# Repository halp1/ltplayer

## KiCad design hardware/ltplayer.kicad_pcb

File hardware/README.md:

# ltplayer hardware

KiCad 10 project, second board layout. Schematic and 4-layer layout are done
and pass ERC and DRC with schematic parity. Not yet fabricated.

| Sheet | Contents |
| --- | --- |
| Power | USB4105 USB-C (5.1k CC pull-downs, USBLC6 ESD), BQ24074 1S LiPo charger with power path (1 A charge, 1.5 A input), soft power latch, TLV75533 3.3 V, TLV62569 buck to 2.0 V feeding two TPS7A2018 1.8 V LDOs (digital `+1V8`, analog `+1V8A`), battery solder pads plus an optional side-entry SMD JST-PH |
| MCU | STM32U575ZIT6Q (SMPS variant, 2.2 uH on VLXSMPS), 16 MHz crystal for USB DFU, decoupling, BOOT0 pull-down, NRST cap, battery and VBUS sense dividers, ten buttons |
| Peripherals | Hirose DM3AT microSD on SDMMC1 4-bit with 47k pull-ups, Newhaven NHD-2.4-240320AF-CSXP 2.4in IPS panel on a 40-pin FH12 on the back, 2N7002 backlight switch |
| Wireless | ESP32-MINI-1U (Bluetooth Classic A2DP, BLE, 2.4 GHz WiFi) on the back, own TLV75733 3.3 V regulator switched by the MCU, U.FL to a stick-on antenna |
| Audio | Two CS43131 (I2C 0x30 and 0x31), shared 22.5792 MHz 1.8 V oscillator for MCLK, PCA9306 I2C shifter, TXS0102 shifters on I2S, four TMUX4819 output switches, SJ1-3524N 3.5 mm and PJ-4450 4.4 mm jacks on the back |

## Pin map

Kept as close to the current firmware (`src/main.rs`) as possible.

| Function | Pin | Notes |
| --- | --- | --- |
| SDMMC1 D0 D1 D2 D3 CLK CMD | PC8 PC9 PC10 PC11 PC12 PD2 | unchanged |
| SD card detect | PF15 | low = card present |
| SPI1 SCK MOSI | PA5 PA7 | unchanged, panel MISO (SDO) not connected |
| TFT CS DC RST | PD14 PD15 PF12 | unchanged, 4-wire SPI strapped by IM0/IM1/IM2 |
| Backlight | PE11 | TIM1_CH2 PWM into Q301, high = on |
| Buttons up down left right | PE13 PE14 PA3 PA2 | front d-pad, active low with internal pull-up |
| Buttons play/pause back | PE10 PB0 | play/pause moved from PC3 so every button has its own EXTI line |
| Button menu | PE15 | active high, shares the BOOT0 net (see Flashing) |
| Buttons vol+ vol- | PE7 PE8 | right edge SKSC, active low with internal pull-up |
| Power button | PE12 | active high, VSYS through a 100k/200k divider |
| Power hold | PC13 | drive high at boot to keep the regulators on |
| SAI1 FS_A SCK_A SD_A | PE4 PE5 PE6 | |
| DAC INT | PE1 | moved from PE2, which shared an EXTI line with the right button |
| DAC reset control | PE3 | inverted through Q401: low releases reset, high or floating holds it |
| I2C1 SCL SDA | PB8 PB9 | |
| JACK_SEL | PG0 | low = 3.5 mm |
| Output switch enable | PG3 | SW_EN, high turns on all four TMUX4819, low mutes both jacks |
| Jack detect 3.5 mm, 4.4 mm | PG1, PG2 | |
| USB DM DP, VBUS sense | PA11 PA12, PA9 | |
| Battery sense | PA0 | VBAT / 2 |
| BOOT0 | PH3 | 10k to GND, the menu button pulls it to +3V3 |
| ESP32 UART (USART3 TX, RX) | PD8 PD9 | commands and ESP32 firmware updates |
| ESP32 I2S (SAI2_A SCK, SD, FS) | PD10 PD11 PD12 | MCU sends decoded audio to the ESP32 |
| ESP32 EN, BOOT, radio power | PD13 PG13 PG14 | PG14 high turns on the ESP32's 3.3 V regulator |
| HSE | PH0 PH1 | 16 MHz crystal Y201 |

## Power

The slide switch is gone. SW101 pulls `PWR_EN` up from VSYS through D103, which
starts all three regulators. Firmware then drives PC13 high, which holds
`PWR_EN` through D104, so the board stays on after the button is released. To
power off, drive PC13 low. R107 pulls `PWR_EN` down so the board stays off
while the button is up. PE12 reads the button through a divider so it also
works as a normal input while running.

USB power also holds `PWR_EN` through R110 and D105, so a plugged-in board
stays on whatever the firmware does. If the user switches off while it is
plugged in, firmware should turn the screen off and sleep.

The BQ24074 runs the system from USB and charges the battery at the same
time (R103 890 ohm sets 1.0 A, R105 1.1k sets a 1.5 A input limit, R111 10k
stands in for a thermistor). The TLV62569 buck (232k/100k divider, 2.2 uH)
turns the battery into 2.0 V,
and both 1.8 V LDOs run from that, so they only drop 0.2 V instead of 2 V.

### Battery

| Output | Draw from the battery | For 18 h with 20% margin |
| --- | --- | --- |
| 3.5 mm, one DAC | about 20 mA | 0.44 Ah |
| 4.4 mm balanced, two DACs | about 34 mA | 0.73 Ah |
| Bluetooth headphones | about 107 mA | 2.3 Ah |

Screen off, 0.1 mW per channel into wired headphones, from datasheet typicals
(Cirrus Table 3-19 for the DACs, Espressif's measured 101 mA for ESP32 A2DP
streaming). The screen adds about 36 mA. Bluetooth sets the battery:

| Cell | Bluetooth | 4.4 mm | 3.5 mm |
| --- | --- | --- | --- |
| 2000 mAh | about 15 to 16 h | about 50 h | about 85 h |
| 2500 mAh (if the rating is honest) | about 19 to 20 h | about 62 h | about 105 h |

It charges in about 2 to 2.5 hours at 1 A. Measure a real board before buying
cells in bulk.

The cell is a **506060**-size LiPo pouch: 5.0 x 60 x 60 mm bare, about 62 mm
long with its protection board, 3.7 V. Makers rate this size 2000 mAh (for
example DNK, HNF and the Tokopedia/Websong listings of the 505060 and 506060)
and a few sell it as 2500 mAh (Bihuade 506060 on Amazon, with a JST-PH 2.0
plug). Plan on 2000 mAh unless a datasheet shows the higher figure. Buy one
with a protection board (PCM). The BQ24074 has no cell protection of its own.

It lies flat on the back of the board, x -30.5 to +30.5 and y -37 to +25:
between the two bottom screw bosses, and below the two jacks, which sit on
the back along the top edge and are as deep as the battery. Under the cell
the deepest part is the display connector J302 at 2.1 mm, so the cell sits
from Z -2.7 to -7.7. Put a 0.1 mm Kapton sheet between cell and parts and fix
it with thin foam tape. The enclosure needs at least 7.7 mm behind the board
face, plus the foam and a swelling allowance (keep 0.5 mm).

The protection board end faces the top, toward the jacks. Both battery
connectors sit on the back just above the cell's top end and are SMD, so
nothing pokes through to the front. Solder the wires to J103 (right edge, just
below J102, "+" marks VBAT), or for a cell with a JST-PH
plug fit J102 (top right, between the 4.4 mm jack and the right edge, opening
down toward the cell, 3 mm left for the plug). Check the plug's polarity
against J102 pin 1 (VBAT) before connecting: cheap cells differ.

## Bluetooth and WiFi

The ESP32 sits on the back with its own regulator (U107), which the MCU turns
on with PG14 only when wireless is in use, so wired playback pays nothing for
it. The MCU decodes the music as usual and sends it to the ESP32 over I2S,
and the ESP32 streams it to the headphones over Bluetooth A2DP (SBC codec).
Commands go over USART3. The same chip has 2.4 GHz WiFi.

The module uses an external antenna: a small flexible stick-on antenna on a
U.FL cable, placed behind the screen glass or another non-metal part of the
case, at least about 5 mm from metal. The whole case can be metal. Example
antennas: Molex 146153 (about 40 x 7 mm) or any 2.4 GHz FPC antenna with a
U.FL (IPEX MHF I) plug and a short cable.

The ESP32 has its own firmware. The MCU updates it over USART3 by holding
ESP_BOOT low and pulsing ESP_EN, so flashing the whole device stays USB only.

## Display

Newhaven [NHD-2.4-240320AF-CSXP](https://newhavendisplay.com/2-4-inch-ips-tft-without-touchscreen/):
2.4in IPS, 240x320, ST7789VI, mounted landscape with the picture centred on
the board. 4-wire SPI (IM0 low, IM1 and IM2 high on the board). The panel runs
from +3V3. Its four backlight LEDs run from VSYS through R307 (22 ohm),
switched on the low side by Q301 from PE11. Firmware should scale the PWM
duty with the battery reading on PA0 to keep brightness even.

### Fitting the cable

The cable leaves the panel's left edge. Its first 13 mm are 39 mm wide (the
part with the shielding and small parts on it). Then a 20.5 mm wide, 0.3 mm
thick tail runs another 16.8 mm to the contacts. Newhaven designed it to fold
flat behind the panel, and the board is laid out for that:

1. Fold the cable back under the panel, flat against the panel's back. The
   wide part stays on the panel, the narrow tail sticks out past it.
2. Hold the panel above the board, picture up, and feed the tail straight down
   through the slot (1.2 x 22.5 mm, about 11 mm in from the panel's left
   edge). Only the tail goes through, the wide part never enters the slot. Go
   end first, the 0.3 mm tail drops through the 1.2 mm slot with room to
   spare.
3. Turn the board over. Bend the tail flat against the back toward J302,
   whose opening is 6 mm from the slot.
4. Flip up J302's black actuator, push the tail in until it stops (contacts
   down, toward the board), and press the actuator closed.
5. Turn the board back over and lay the panel down onto the front shell. The
   2 mm of spare length bows in the 1.8 mm gap under the panel.

Nothing taller than an 0603 part sits on the front under the folded cable
(x -33.2 to -21.1). The 1.8 V regulators and the buck sit on the back there.

J302 is a bottom-contact Hirose FH12-40S-0.5SH. After the fold and the turn,
the cable's contacts face the board, and its pin order arrives mirrored, so
panel pin 1 is on J302 pin 40. The schematic is wired that way. The front
shell holds the panel with adhesive.

## Flashing

Flashing is USB only. The STM32's built-in USB DFU bootloader does the work,
so no probe or back plate removal is needed.

1. Hold the menu button and plug in USB. Menu pulls BOOT0 high, so the chip
   starts in its bootloader. Firmware can also jump there from a menu item.
2. Flash: `dfu-util -a 0 -s 0x08000000:leave -D ltplayer.bin`, or use
   STM32CubeProgrammer in USB mode.

There is no debug header. Use `defmt` logging over USB for debugging.

## Audio routing

Four TMUX4819 (one SPDT each, WSON-8 2 x 2 mm, 0.16 ohm) do the routing.
JACK_SEL drives all four SEL pins (low selects SA, high selects SB). SW_EN
(PG3) drives all four EN pins: low turns every switch off, which mutes both
jacks, for example while the DACs start up.

* Low: U406 and U407 pass DAC1 HPOUTA and HPOUTB to the 3.5 mm tip and ring. DAC1 runs in stereo. U408 and U409 are open, so DAC2 is disconnected.
* High: U406 and U407 pass DAC1 to 4.4 mm L+ and L-, U408 and U409 connect DAC2 to R+ and R-. Both DACs run in mono (differential) mode, set by the register sequence in datasheet section 5.12.

Both DAC resets are held low by Q401 until firmware drives PE3 low, and R448
pulls `DAC_RESET` to VSYS, so VP is up before reset releases as the datasheet
requires. HPREFA/HPREFB of both DACs and the jack sleeves share `HP_GND`, a
dedicated In2 trace that joins `GND` only at R453 (0 ohm).

## Board

67.0 x 94.6 mm, 6.15 mm corner radius, which leaves 0.2 mm per side in the
67.4 x 95 enclosure pocket. Four layers:

| Layer | Use |
| --- | --- |
| F.Cu | parts, signals, GND fill |
| In1.Cu | solid GND |
| In2.Cu | +3V3 with a +1V8 island under the DACs and level shifters (notched for the display connector), VSYS and HP_GND traces |
| B.Cu | signals, microSD, display and battery connectors, GND fill |

Rules are in `ltplayer.kicad_pro` and sized for JLCPCB 4-layer: 0.1 mm
track and space minimum, 0.127 mm clearance, 0.45/0.25 mm vias. No via-in-pad
or blind vias.

### Parts for reflow

Every resistor and capacitor is 0603 or bigger (109 at 0603, 7 at 0805), and
so are both inductors. The finest-pitch parts are the two CS43131 DACs (QFN
0.4 mm, no larger package exists) and the parts at 0.5 mm pitch: the
STM32U575 (LQFP-144), the BQ24074 (QFN 3 x 3), the four TMUX4819 (WSON 2 x 2)
and the display connector. Everything else has leads at 0.65 mm or wider:
SSOP-8 level shifters (PCA9306DCTR, TXS0102DCTR), SOT-23 regulators
including the TLV62569 buck, a 3.2 x 2.5 mm crystal and MCLK oscillator
(Epson SG-8018CE class, 1.8 V, 22.5792 MHz). A stencil (0.12 mm) and reflow
handle all of it.
`ltplayer.kicad_dru` relaxes hole clearance inside the USB-C footprint only,
where GCT's land pattern puts the GND pads 0.194 mm from the plastic pegs.

## Mechanical

[ltplayer-mech.dxf](docs/ltplayer-mech.dxf) and
[ltplayer-mech.csv](docs/ltplayer-mech.csv) have the outline, every hole and
the body outlines of the edge parts. Origin at the board centre, +X right,
+Y up, viewed from the front (display side), millimetres.

| Feature | Position | Size |
| --- | --- | --- |
| Corner holes H101 to H104 | (±27.35, ±41.15) | 2.2 mm plated, 4.4 mm GND pad, M2. PCB mount and back plate screws share them |
| Display panel | x -32.41 to +27.50, y -4.30 to +38.50 | 59.91 x 42.80 x 2.55 |
| Picture area | x -24.48 to +24.48, y -1.26 to +35.46 | 48.96 x 36.72, the window, centred |
| Display cable slot | x -20.91 to -19.71, y +6.35 to +27.85 | through the board, rounded ends |
| 3.5 mm jack J401 | x = -15.0, top edge, back | board notch 4.4 wide, 1.4 deep, opening centre Z -2.6 |
| 4.4 mm jack J402 | x = +15.0, top edge, back | body overhangs the edge by 1.6 mm, opening centre Z -3.3 (estimate) |
| USB-C J101 | x = -14.5, bottom edge, back | opening centre Z about -1.6 |
| microSD J301 | x = +16.5, bottom edge, back | |
| Power, vol+, vol- | x = +31.15, y = +31.5, +17.5, +7.5 | right edge, side push |
| D-pad | centre (0, -28.5), up (0, -18.5), down (0, -38.5), left (-10, -28.5), right (+10, -28.5) | KMR2, play/pause in the middle |
| Back, menu | (-19, -13), (+19, -13) | KMR2 |
| Battery | x -30.5 to +30.5, y -37 to +25 | back, 61 x 62 x 5.0, Z -7.7 to -2.7 |
| Battery pads J103, JST-PH J102 | (+31.0, +23.8), (+24.6, +32.6) | back, above the battery's top end, SMD |
| Display connector J302 | (-9.3, +17.1) | back, opening faces the cable slot |
| ESP32 U501 | (+18.0, -10.5) | back, 13.2 x 13.5 x 2.4, U.FL at its top left corner |

### 3D

`3d/ltplayer-assembly.step` is the board with every part and the display
panel, drawn from its datasheet with the picture area and the folded cable
as separate solids, and the battery as a block. It uses the same origin as the DXF, with +Z toward the
user and the board's back face at Z = 0. `3d/ltplayer-board.step` is the
board alone. Both are build outputs and not in git. Run `scripts/route.sh`, or
only the last block of it, to make them.

| Item | Z (mm) |
| --- | --- |
| Battery back face | -7.7 |
| Back of the 4.4 mm jack (estimate) | -6.6 |
| Back of the 3.5 mm jack | -5.6 |
| Battery front face | -2.7 |
| Back of the ESP32 module | -2.4 |
| Board back face, front face | 0, 1.6 |
| KMR2 button tops | 3.5 |
| Display panel back, glass front | 3.4, 5.95 |

Total from battery back to glass: 13.65 mm (it was 18.75 mm with the jacks
on the front). The panel sits 0.3 mm above the tallest part under it, the
STM32 (LQFP-144, 1.5 mm). Both jacks are on the back, so their pins poke out
of the front: trim them to 1 mm after soldering. The jacks are as deep as the
battery, so they add nothing behind it.

Parts with no model in KiCad's library are plain blocks named `placeholder`:
the three side buttons (1.25 mm tall per Alps), the four TMUX4819 (0.8 mm),
the MCLK oscillator (0.8 mm), the 4.4 mm jack and the SMD JST-PH (4.9 mm, about as tall as the through-hole one). KKG publishes no height for
the PJ-4450, so its 6.6 mm block is an estimate.

## Rebuilding the layout

The board is generated from the schematic by scripts. Hand edits in KiCad are
lost on the next run, so change the scripts instead.

```sh
scripts/route.sh   # 5 to 15 minutes
```

| Script | Step |
| --- | --- |
| `geom.py` | shared numbers: outline, DAC cells, plane split, net classes |
| `localize_fp.py` | copies edge-hanging footprints into `ltplayer.pretty` without edge and silk outlines |
| `build.py` | new board from the netlist, anchors the big parts, draws the outline |
| `place_passives.py` | places the rest next to the pin each one serves |
| `rules.py` | design rules and net classes |
| `plane_vias.py` | a via at every GND, +3V3, +1V8, VSYS and HP_GND pad |
| `dsn2l.py` | presents the board to Freerouting as two layers without the plane nets |
| `finish.sh` | imports the route, runs `trunk.py` (VSYS and HP_GND on In2), pours zones, removes leftovers, `nudge.py` (micron misses at stub vias), DRC |
| `mech.py` | the DXF and CSV above |

Needs Freerouting 2.5 and Java (`FREEROUTING` overrides the jar path) and the
KiCad Python at `~/code/pkg/mcp/kicad/venv`.

## Check before ordering

* **Display cable**: J302 is bottom contact with the pin order mirrored (panel pin 1 on J302 pin 40), worked out from Newhaven's drawing. Check with a paper strip cut to the drawing (contacts marked) before ordering. If it comes out the other way, a top-contact FH12A-40S-0.5SH fits the same footprint area.
* **Display slot**: check the cable folds and drops through the 1.2 mm slot without kinking, with the same paper mock-up.
* **Battery**: confirm the real cell measures 61 x 62 x 5 mm or less with its protection board and wires, and the plug polarity matches J102.
* **Jack openings**: the jacks now face out of the top edge just behind the board (centre about Z -2.6 and -3.3). Check the enclosure opening lines up with a real PJ-4450, whose height is still an estimate.
* **MCLK oscillator**: the footprint is a generic 3.2 x 2.5 mm 4-pad oscillator. Pick a 1.8 V 22.5792 MHz part in that size (Epson SG-8018CE, SiTime SiT1602 class) and check its pad map: 1 OE, 2 GND, 3 OUT, 4 VDD.
* **Charger heat**: 1 A from 5 V into a 3.7 V cell burns about 1.3 W in the BQ24074. It throttles itself if it gets hot, so the real charge time may be longer.
* **Antenna**: try the stick-on antenna in the real case before ordering boards. Signal through the screen glass is weaker near the display's metal frame, so test a few spots.
* **ESP32 footprint**: from Espressif's own KiCad library. Check it against the datasheet land pattern.
* **Bluetooth certification**: selling a product that says Bluetooth needs Bluetooth SIG qualification (USD 12,000 for the first product with this design). The module's FCC/CE approval carries over.
* **DFU clock**: AN2606 may let the STM32U575 bootloader run USB without a crystal. If it does, Y201 can stay unpopulated.
* **microSD**: the slot faces the bottom edge on the back. Confirm the card goes in where the enclosure leaves an opening.
* **4.4 mm jack**: the PJ-4450 pin assignment is estimated from the drawing. Confirm against the part.
* **Side buttons**: the SKSC peg hole spacing is scaled from the Alps drawing. Confirm against a part.
* **3.5 mm detect**: the SJ1-3524N tip switch reads through a 1M pull-up, so detect polarity flips against the 4.4 mm jack.
* **DAC RESET** comes from VSYS through R448. Check the VIH spec at low battery.

## Firmware changes

* Drive PC13 high early in boot to hold power, read the power button on PE12. On USB power, sleep instead of releasing PC13.
* PE3 drives reset through an inverter now: low releases both DACs.
* Buttons: up PE13, down PE14, play/pause PE10, vol+ PE7, vol- PE8 (active low). Menu PE15 is active high. DAC_INT moved to PE1.
* Display: landscape (320x240), ST7789VI on 4-wire SPI without MISO, backlight PWM on TIM1_CH2 (PE11) scaled with battery voltage.
* An "update" menu item that jumps to the system bootloader for USB DFU.
* Bluetooth: SAI2 block A as I2S master to the ESP32, USART3 command link, PG14 to power the ESP32, and an ESP32 firmware (ESP-IDF A2DP source) that the MCU can flash over USART3.
* SAI1 pins, the second DAC at 0x31, mono mode switching and the 3.5 mm detect polarity in `src/jack.rs`.
* Output switches: drive PG3 (SW_EN) high to unmute once the DACs are running, low before switching JACK_SEL or powering down.

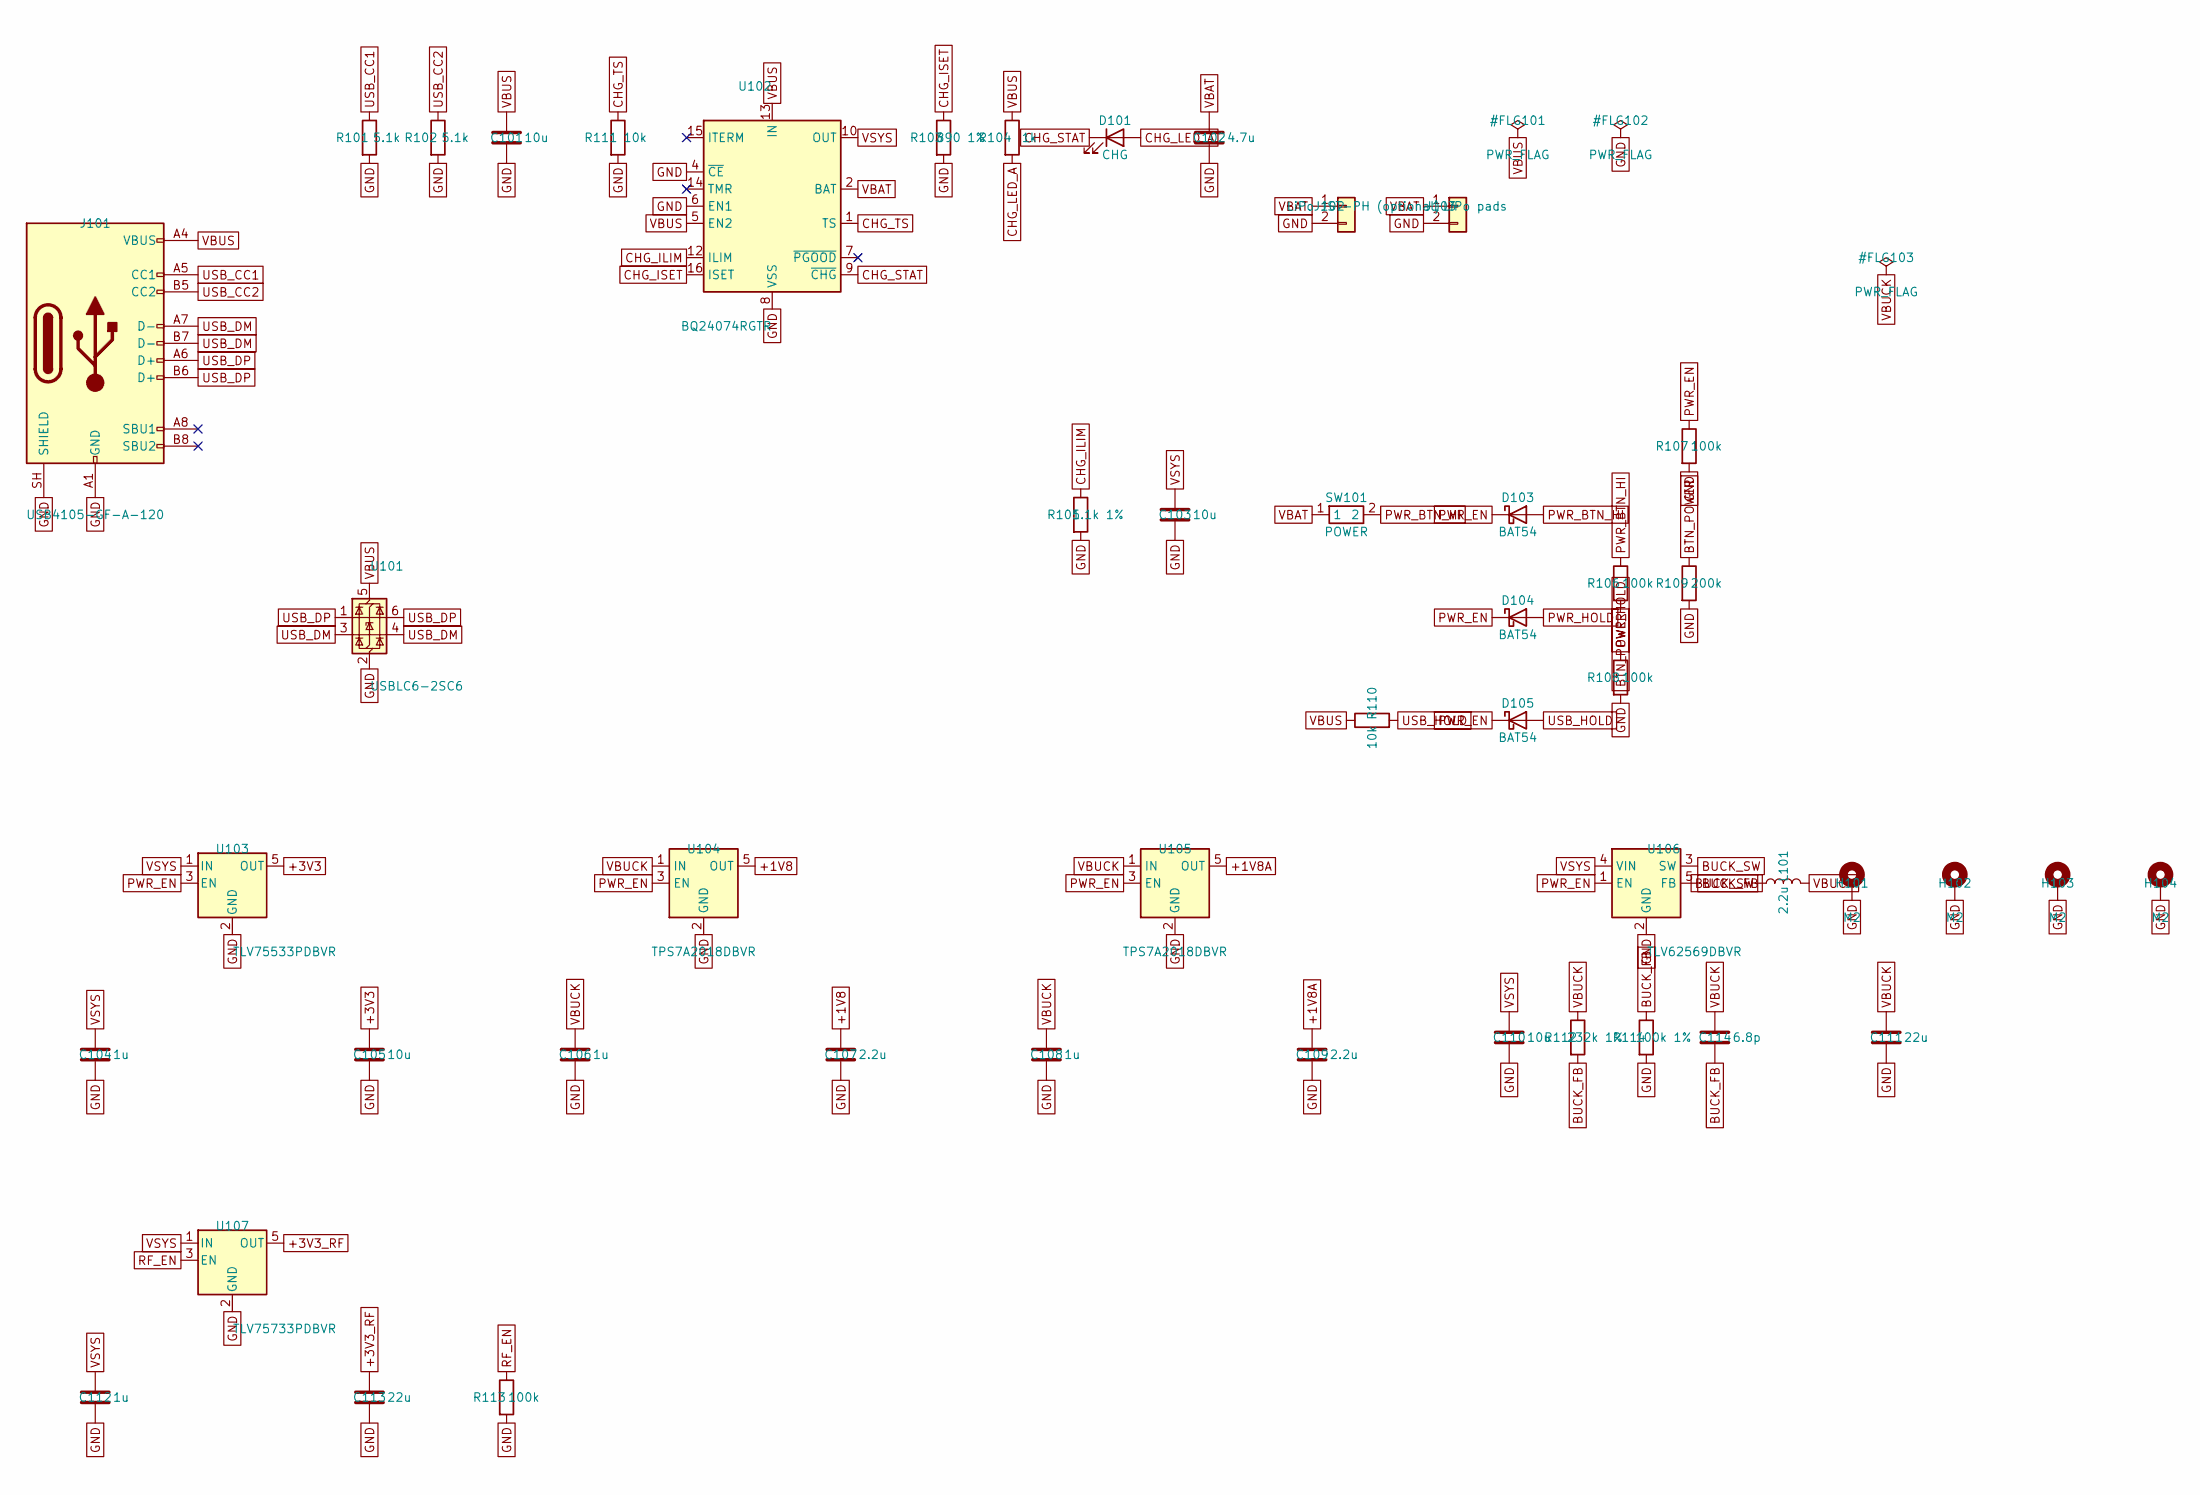
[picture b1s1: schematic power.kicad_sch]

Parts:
C101, C103, C105: 10u; C_0805_2012Metric
C102: 4.7u; C_0805_2012Metric
C104, C106, C108, C112: 1u; C_0603_1608Metric
C107, C109: 2.2u; C_0603_1608Metric
C110: 10u; C_0603_1608Metric
C111, C113: 22u; C_0805_2012Metric
C114: 6.8p; C_0603_1608Metric
D101: CHG; LED_0603_1608Metric
D103, D104, D105: BAT54; D_SOD-323
H101, H102, H103, H104: M2; MountingHole_2.2mm_M2_Pad_Via
J101: USB4105-GF-A-120; USB_C_Receptacle_GCT_USB4105-xx-A_16P_TopMnt_Horizontal
J102: LiPo JST-PH (optional); JST_PH_S2B-PH-SM4-TB_1x02-1MP_P2.00mm_Horizontal
J103: LiPo pads; SolderPads_1x02_SMD_2x3mm_P4mm
L101: 2.2u; L_0805_2012Metric
R101, R102: 5.1k; R_0603_1608Metric
R103: 890 1%; R_0603_1608Metric
R104: 1k; R_0603_1608Metric
R105: 1.1k 1%; R_0603_1608Metric
R106, R107, R108, R113: 100k; R_0603_1608Metric
R109: 200k; R_0603_1608Metric
R110, R111: 10k; R_0603_1608Metric
R112: 232k 1%; R_0603_1608Metric
R114: 100k 1%; R_0603_1608Metric
SW101: POWER; SW_Alps_SKSC_SidePush
U101: USBLC6-2SC6; SOT-23-6
U102: BQ24074RGTR; VQFN-16-1EP_3x3mm_P0.5mm_EP1.6x1.6mm
U103: TLV75533PDBVR; SOT-23-5
U104, U105: TPS7A2018DBVR; SOT-23-5
U106: TLV62569DBVR; SOT-23-5
U107: TLV75733PDBVR; SOT-23-5

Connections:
+1V8: C107.1, U104.5 (OUT); also elsewhere on the board
+1V8A: C109.1, U105.5 (OUT); also elsewhere on the board
+3V3: C105.1, U103.5 (OUT); also elsewhere on the board
+3V3_RF: C113.1, U107.5 (OUT); also elsewhere on the board
BTN_POWER: R106.2, R109.1; also elsewhere on the board
BUCK_FB: C114.2, R112.2, R114.1, U106.5 (FB)
BUCK_SW: L101.1, U106.3 (SW)
CHG_ILIM: R105.1, U102.12 (ILIM)
CHG_ISET: R103.1, U102.16 (ISET)
CHG_LED_A: D101.2 (A), R104.2
CHG_STAT: D101.1 (K), U102.9 (~CHG)
CHG_TS: R111.1, U102.1 (TS)
GND: C101.2, C102.2, C103.2, C104.2, C105.2, C106.2, C107.2, C108.2, C109.2, C110.2, C111.2, C112.2, C113.2, H101.1, H102.1, H103.1, H104.1, J101.A1 (GND), J101.A12 (GND), J101.B1 (GND), J101.B12 (GND), J101.SH (SHIELD), J102.2, J103.2, R101.2, R102.2, R103.2, R105.2, R107.2, R108.2, R109.2, R111.2, R113.2, R114.2, U101.2 (GND), U102.4 (~CE), U102.6 (EN1), U102.8 (VSS), U102.17 (VSS), U103.2 (GND), U104.2 (GND), U105.2 (GND), U106.2 (GND), U107.2 (GND); also elsewhere on the board
PWR_BTN_HI: D103.2 (A), R106.1, SW101.2
PWR_EN: D103.1 (K), D104.1 (K), D105.1 (K), R107.1, U103.3 (EN), U104.3 (EN), U105.3 (EN), U106.1 (EN)
PWR_HOLD: D104.2 (A), R108.1; also elsewhere on the board
RF_EN: R113.1, U107.3 (EN); also elsewhere on the board
USB_CC1: J101.A5 (CC1), R101.1
USB_CC2: J101.B5 (CC2), R102.1
USB_DM: J101.A7 (D-), J101.B7 (D-), U101.3 (I/O2), U101.4 (I/O2); also elsewhere on the board
USB_DP: J101.A6 (D+), J101.B6 (D+), U101.1 (I/O1), U101.6 (I/O1); also elsewhere on the board
USB_HOLD: D105.2 (A), R110.2
VBAT: C102.1, J102.1, J103.1, SW101.1, U102.2 (BAT), U102.3 (BAT); also elsewhere on the board
VBUCK: C106.1, C108.1, C111.1, C114.1, L101.2, R112.1, U104.1 (IN), U105.1 (IN)
VBUS: C101.1, J101.A4 (VBUS), J101.A9 (VBUS), J101.B4 (VBUS), J101.B9 (VBUS), R104.1, R110.1, U101.5 (VBUS), U102.5 (EN2), U102.13 (IN); also elsewhere on the board
VSYS: C103.1, C104.1, C110.1, C112.1, U102.10 (OUT), U102.11 (OUT), U103.1 (IN), U106.4 (VIN), U107.1 (IN); also elsewhere on the board

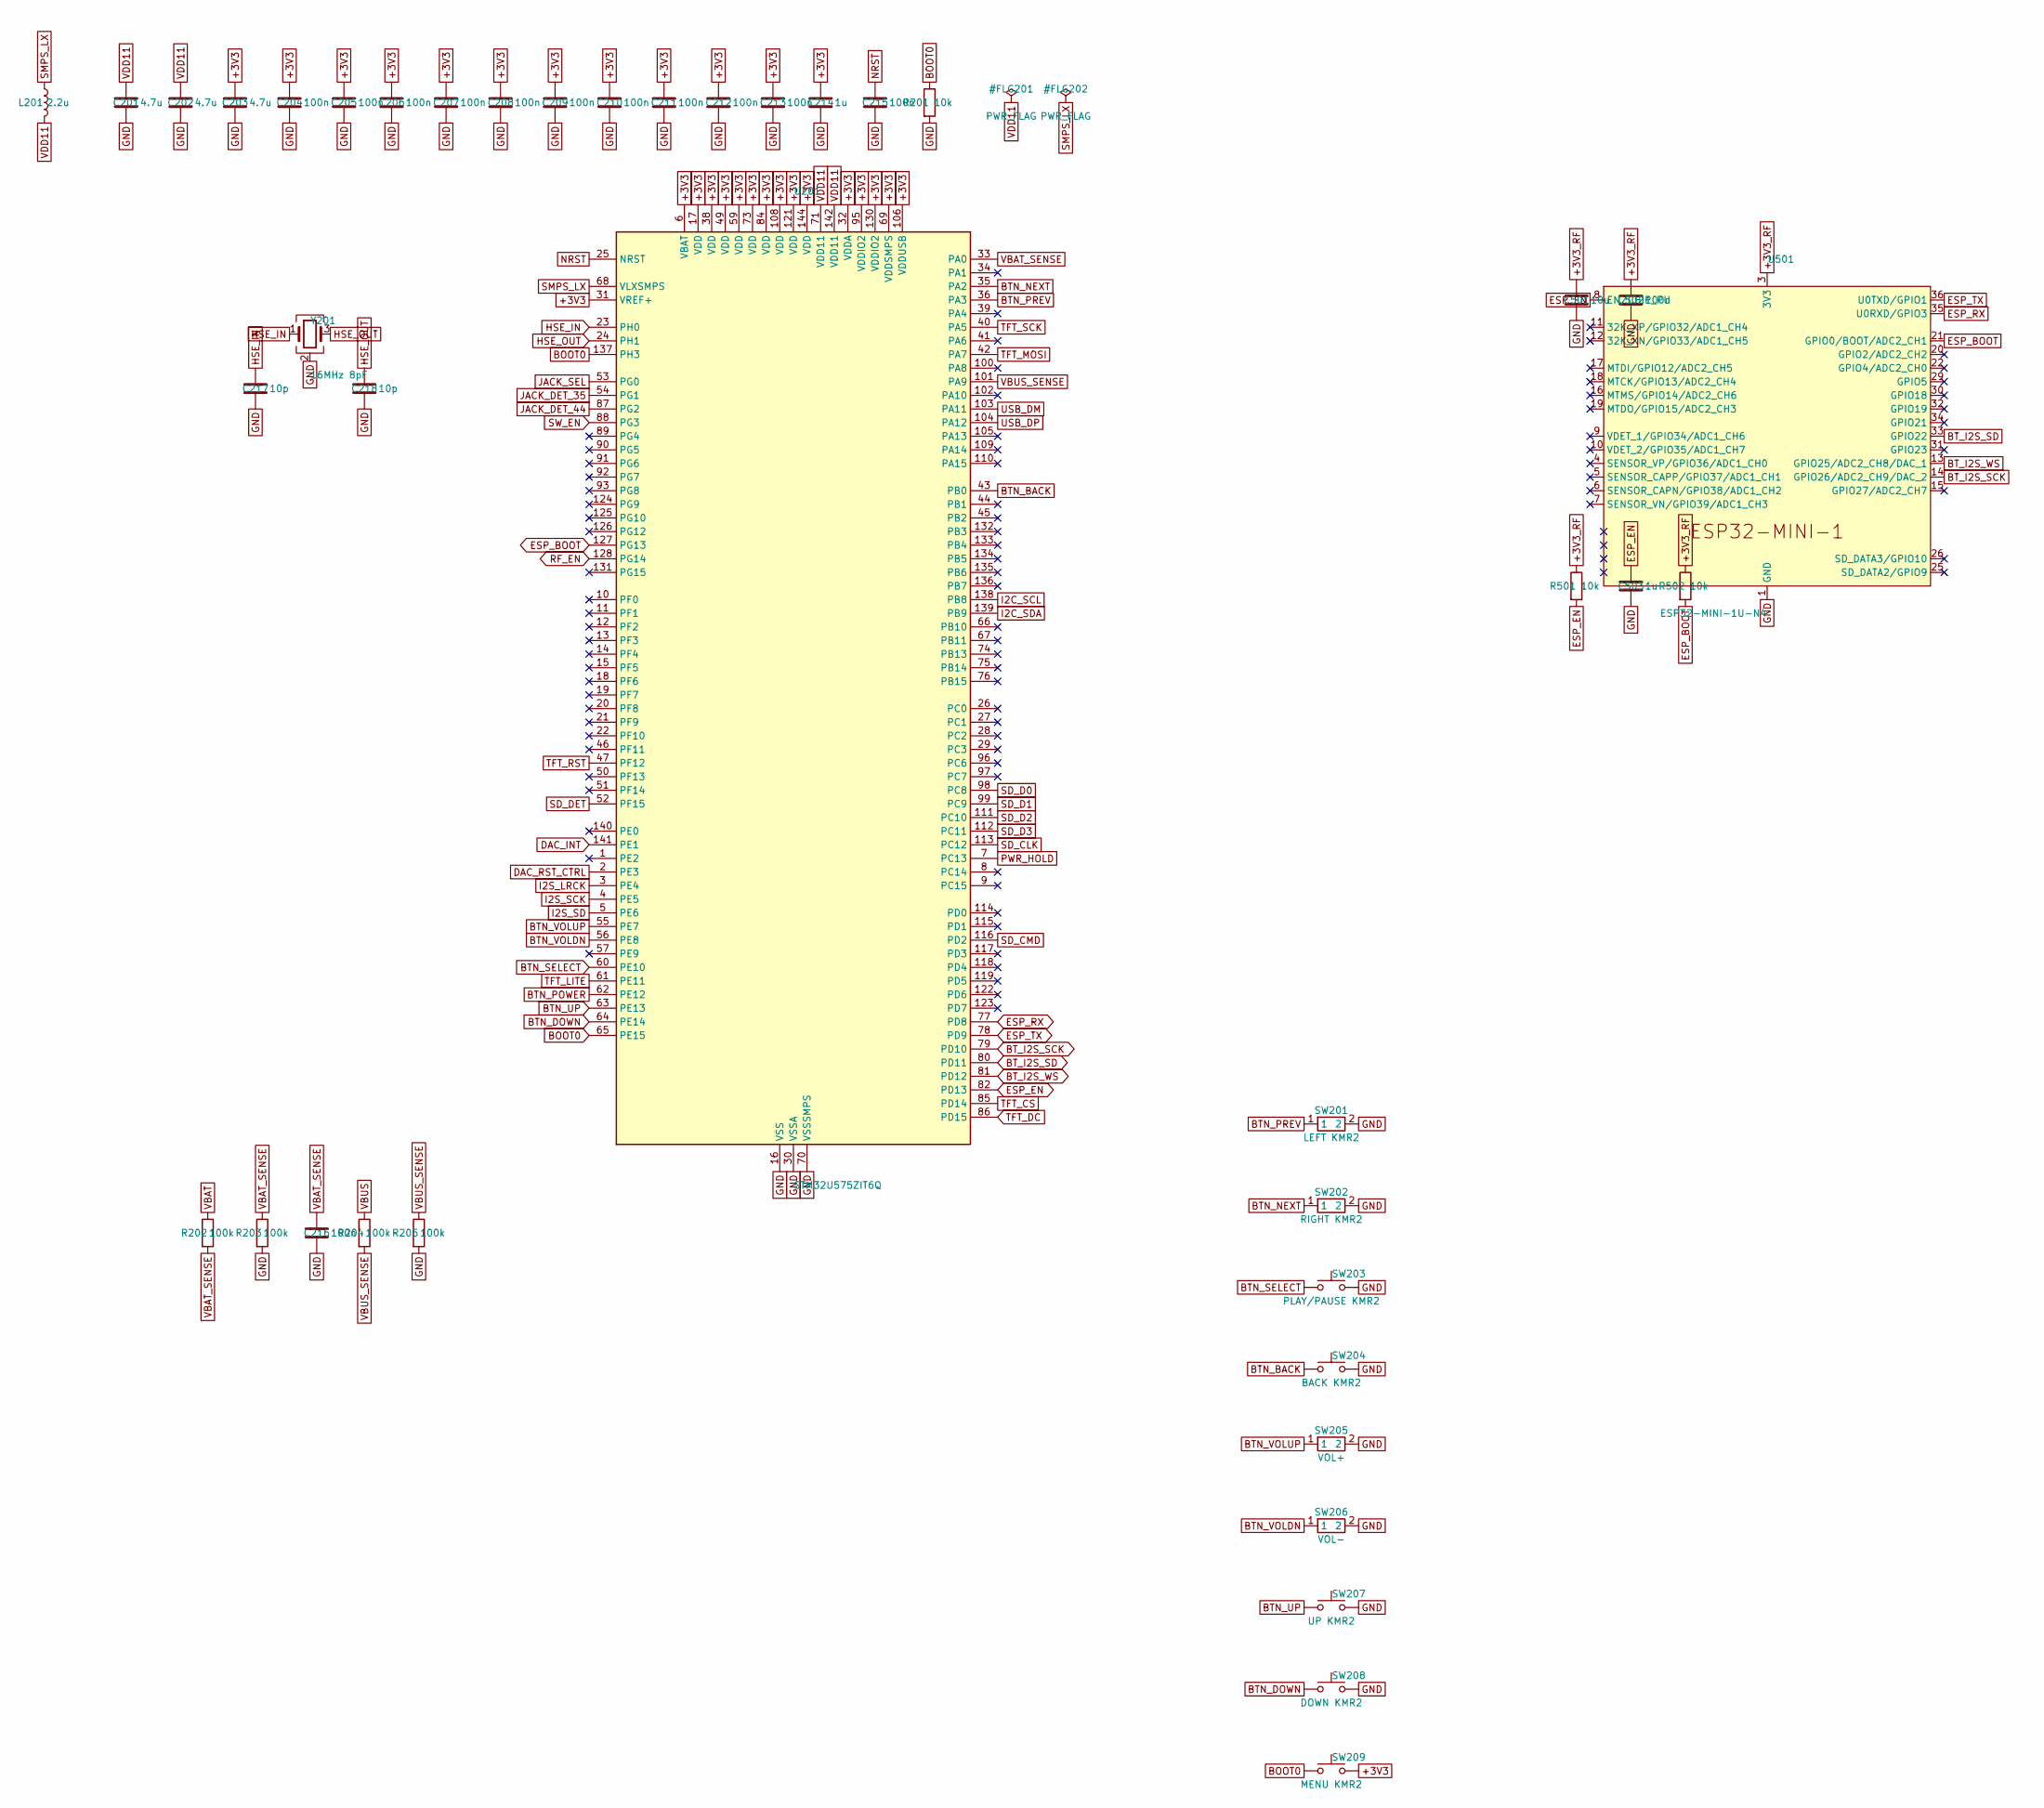
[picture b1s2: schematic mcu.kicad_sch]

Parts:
C201, C202, C203: 4.7u; C_0603_1608Metric
C204, C205, C206, C207, C208, C209, C210, C211, C212, C213, C215, C216, C502: 100n; C_0603_1608Metric
C214, C503: 1u; C_0603_1608Metric
C217, C218: 10p; C_0603_1608Metric
C501: 10u; C_0603_1608Metric
L201: 2.2u; L_0805_2012Metric
R201, R501, R502: 10k; R_0603_1608Metric
R202, R203, R204, R205: 100k; R_0603_1608Metric
SW201: LEFT KMR2; SW_Push_1P1T_NO_CK_KMR2
SW202: RIGHT KMR2; SW_Push_1P1T_NO_CK_KMR2
SW203: PLAY/PAUSE KMR2; SW_Push_1P1T_NO_CK_KMR2
SW204: BACK KMR2; SW_Push_1P1T_NO_CK_KMR2
SW205: VOL+; SW_Alps_SKSC_SidePush
SW206: VOL-; SW_Alps_SKSC_SidePush
SW207: UP KMR2; SW_Push_1P1T_NO_CK_KMR2
SW208: DOWN KMR2; SW_Push_1P1T_NO_CK_KMR2
SW209: MENU KMR2; SW_Push_1P1T_NO_CK_KMR2
U201: STM32U575ZIT6Q; LQFP-144_20x20mm_P0.5mm
U501: ESP32-MINI-1U-N4; ESP32-MINI-1U
Y201: 16MHz 8pF; Crystal_SMD_3225-4Pin_3.2x2.5mm

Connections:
+3V3: C203.1, C204.1, C205.1, C206.1, C207.1, C208.1, C209.1, C210.1, C211.1, C212.1, C213.1, C214.1, SW209.2, U201.6 (VBAT), U201.17 (VDD), U201.31 (VREF+), U201.32 (VDDA), U201.38 (VDD), U201.49 (VDD), U201.59 (VDD), U201.69 (VDDSMPS), U201.73 (VDD), U201.84 (VDD), U201.95 (VDDIO2), U201.106 (VDDUSB), U201.108 (VDD), U201.121 (VDD), U201.130 (VDDIO2), U201.144 (VDD); also elsewhere on the board
+3V3_RF: C501.1, C502.1, R501.1, R502.1, U501.3 (3V3); also elsewhere on the board
BOOT0: R201.1, SW209.1, U201.65 (PE15), U201.137 (PH3)
BTN_BACK: SW204.1, U201.43 (PB0)
BTN_DOWN: SW208.1, U201.64 (PE14)
BTN_NEXT: SW202.1, U201.35 (PA2)
BTN_POWER: U201.62 (PE12); also elsewhere on the board
BTN_PREV: SW201.1, U201.36 (PA3)
BTN_SELECT: SW203.1, U201.60 (PE10)
BTN_UP: SW207.1, U201.63 (PE13)
BTN_VOLDN: SW206.1, U201.56 (PE8)
BTN_VOLUP: SW205.1, U201.55 (PE7)
BT_I2S_SCK: U201.79 (PD10), U501.14 (GPIO26/ADC2_CH9/DAC_2)
BT_I2S_SD: U201.80 (PD11), U501.33 (GPIO22)
BT_I2S_WS: U201.81 (PD12), U501.13 (GPIO25/ADC2_CH8/DAC_1)
DAC_INT: U201.141 (PE1); also elsewhere on the board
DAC_RST_CTRL: U201.2 (PE3); also elsewhere on the board
ESP_BOOT: R502.2, U201.127 (PG13), U501.21 (GPIO0/BOOT/ADC2_CH1)
ESP_EN: C503.1, R501.2, U201.82 (PD13), U501.8 (EN/CHIP_PU)
ESP_RX: U201.77 (PD8), U501.35 (U0RXD/GPIO3)
ESP_TX: U201.78 (PD9), U501.36 (U0TXD/GPIO1)
GND: C201.2, C202.2, C203.2, C204.2, C205.2, C206.2, C207.2, C208.2, C209.2, C210.2, C211.2, C212.2, C213.2, C214.2, C215.2, C216.2, C217.2, C218.2, C501.2, C502.2, C503.2, R201.2, R203.2, R205.2, SW201.2, SW202.2, SW203.2, SW204.2, SW205.2, SW206.2, SW207.2, SW208.2, U201.16 (VSS), U201.30 (VSSA), U201.37 (VSS), U201.48 (VSS), U201.58 (VSS), U201.70 (VSSSMPS), U201.72 (VSS), U201.83 (VSS), U201.94 (VSS), U201.107 (VSS), U201.120 (VSS), U201.129 (VSS), U201.143 (VSS), U501.1 (GND), U501.2 (GND), U501.27 (GND), U501.38 (GND), U501.39 (GND), U501.40 (GND), U501.41 (GND), U501.42 (GND), U501.43 (GND), U501.44 (GND), U501.45 (GND), U501.46 (GND), U501.47 (GND), U501.48 (GND), U501.49 (GND), U501.50 (GND), U501.51 (GND), U501.52 (GND), U501.53 (GND), U501.54 (GND), U501.55 (GND), Y201.2 (G), Y201.4 (G); also elsewhere on the board
HSE_IN: C217.1, U201.23 (PH0), Y201.1
HSE_OUT: C218.1, U201.24 (PH1), Y201.3
I2C_SCL: U201.138 (PB8); also elsewhere on the board
I2C_SDA: U201.139 (PB9); also elsewhere on the board
I2S_LRCK: U201.3 (PE4); also elsewhere on the board
I2S_SCK: U201.4 (PE5); also elsewhere on the board
I2S_SD: U201.5 (PE6); also elsewhere on the board
JACK_DET_35: U201.54 (PG1); also elsewhere on the board
JACK_DET_44: U201.87 (PG2); also elsewhere on the board
JACK_SEL: U201.53 (PG0); also elsewhere on the board
NRST: C215.1, U201.25 (NRST)
PWR_HOLD: U201.7 (PC13); also elsewhere on the board
RF_EN: U201.128 (PG14); also elsewhere on the board
SD_CLK: U201.113 (PC12); also elsewhere on the board
SD_CMD: U201.116 (PD2); also elsewhere on the board
SD_D0: U201.98 (PC8); also elsewhere on the board
SD_D1: U201.99 (PC9); also elsewhere on the board
SD_D2: U201.111 (PC10); also elsewhere on the board
SD_D3: U201.112 (PC11); also elsewhere on the board
SD_DET: U201.52 (PF15); also elsewhere on the board
SMPS_LX: L201.1, U201.68 (VLXSMPS)
SW_EN: U201.88 (PG3); also elsewhere on the board
TFT_CS: U201.85 (PD14); also elsewhere on the board
TFT_DC: U201.86 (PD15); also elsewhere on the board
TFT_LITE: U201.61 (PE11); also elsewhere on the board
TFT_MOSI: U201.42 (PA7); also elsewhere on the board
TFT_RST: U201.47 (PF12); also elsewhere on the board
TFT_SCK: U201.40 (PA5); also elsewhere on the board
USB_DM: U201.103 (PA11); also elsewhere on the board
USB_DP: U201.104 (PA12); also elsewhere on the board
VBAT: R202.1; also elsewhere on the board
VBAT_SENSE: C216.1, R202.2, R203.1, U201.33 (PA0)
VBUS: R204.1; also elsewhere on the board
VBUS_SENSE: R204.2, R205.1, U201.101 (PA9)
VDD11: C201.1, C202.1, L201.2, U201.71 (VDD11), U201.142 (VDD11)

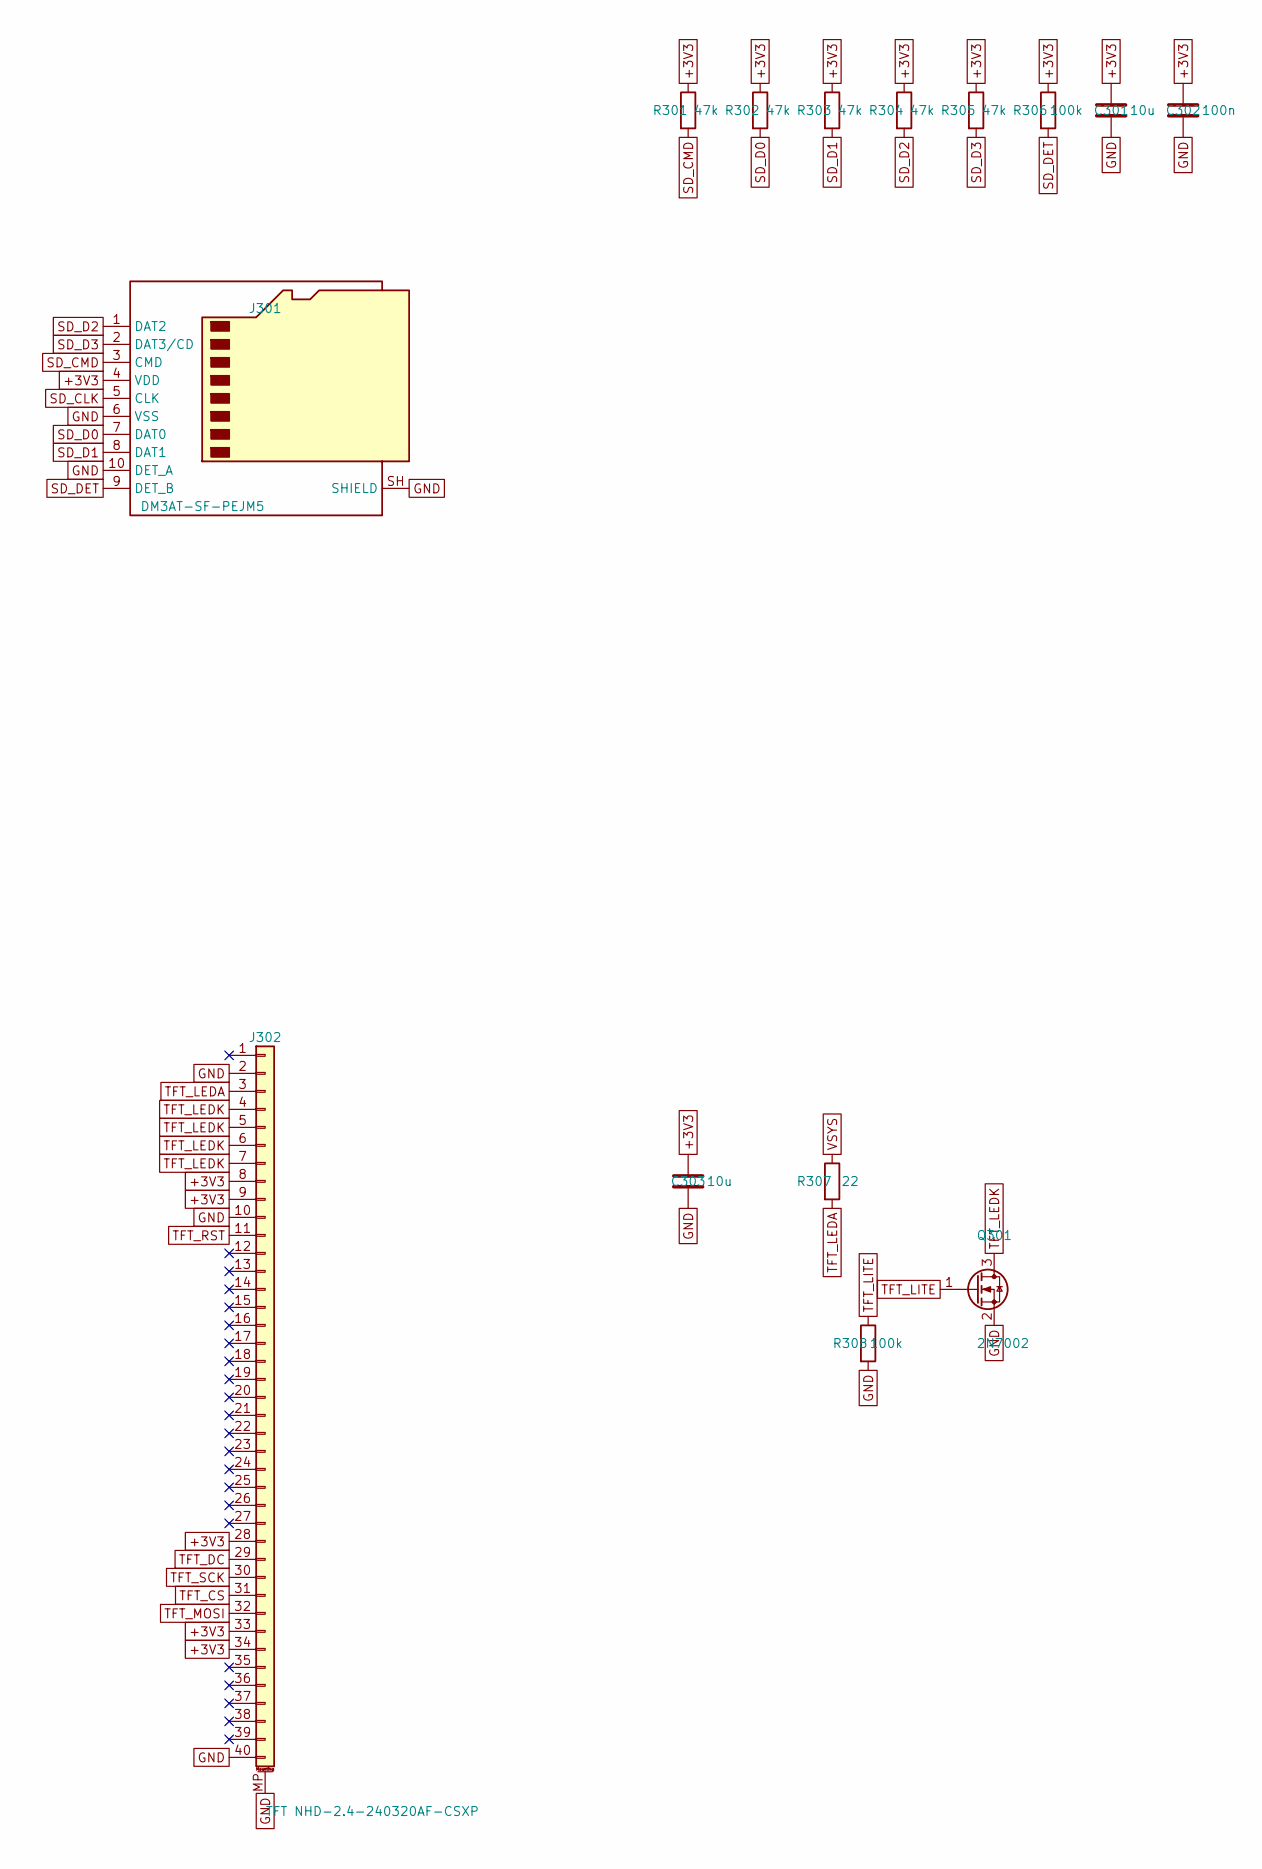
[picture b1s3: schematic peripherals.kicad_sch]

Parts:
C301, C303: 10u; C_0603_1608Metric
C302: 100n; C_0603_1608Metric
J301: DM3AT-SF-PEJM5; microSD_HC_Hirose_DM3AT-SF-PEJM5
J302: TFT NHD-2.4-240320AF-CSXP; Hirose_FH12-40S-0.5SH_1x40-1MP_P0.50mm_Horizontal
Q301: 2N7002; SOT-23
R301, R302, R303, R304, R305: 47k; R_0603_1608Metric
R306, R308: 100k; R_0603_1608Metric
R307: 22; R_0805_2012Metric

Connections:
+3V3: C301.1, C302.1, C303.1, J301.4 (VDD), J302.8, J302.9, J302.28, J302.33, J302.34, R301.1, R302.1, R303.1, R304.1, R305.1, R306.1; also elsewhere on the board
GND: C301.2, C302.2, C303.2, J301.6 (VSS), J301.10 (DET_A), J301.SH (SHIELD), J302.2, J302.10, J302.40, J302.MP (MountPin), Q301.2 (S), R308.2; also elsewhere on the board
SD_CLK: J301.5 (CLK); also elsewhere on the board
SD_CMD: J301.3 (CMD), R301.2; also elsewhere on the board
SD_D0: J301.7 (DAT0), R302.2; also elsewhere on the board
SD_D1: J301.8 (DAT1), R303.2; also elsewhere on the board
SD_D2: J301.1 (DAT2), R304.2; also elsewhere on the board
SD_D3: J301.2 (DAT3/CD), R305.2; also elsewhere on the board
SD_DET: J301.9 (DET_B), R306.2; also elsewhere on the board
TFT_CS: J302.31; also elsewhere on the board
TFT_DC: J302.29; also elsewhere on the board
TFT_LEDA: J302.3, R307.2
TFT_LEDK: J302.4, J302.5, J302.6, J302.7, Q301.3 (D)
TFT_LITE: Q301.1 (G), R308.1; also elsewhere on the board
TFT_MOSI: J302.32; also elsewhere on the board
TFT_RST: J302.11; also elsewhere on the board
TFT_SCK: J302.30; also elsewhere on the board
VSYS: R307.1; also elsewhere on the board

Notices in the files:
parts and their libraries:
ESP32-MINI-1U, external antenna via U.FL. From espressif/kicad-libraries (CC-BY-SA 4.0 with the KiCad design exception): https://github.com/espressif/kicad-libraries
